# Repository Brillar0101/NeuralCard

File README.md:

# NeuralCard

A business card that runs a neural network.

> This is the sponsorship build, a fork of
> [NeuralCard](https://github.com/Brillar0101/NeuralCard) prepared for assembly by
> PCBWay. The BOM has been rewritten from JLCPCB and LCSC part codes into
> manufacturer part numbers PCBWay can quote, with approved alternates where a swap
> is safe and do-not-substitute rules where it is not. Revision v3.0.1-dev corrects
> the BOOT and RESET switch pad mapping after the prototype showed IO0/EN shorted to
> ground. This is still a development board: its latest DRC reports 410 violations
> and 191 schematic-parity issues. See the [verification report](docs/drc/v3.0.1-dev-verification.md)
> before using or fabricating this revision.

It is a credit-card-sized PCB, 85.6 by 54 mm, carrying an ESP32-S3, a 6-axis
IMU, and 24 LEDs laid out as the network it actually runs: 6 input neurons,
8 hidden, 10 output. You hold the card, draw a digit in the air, and the LEDs
light with the real activations as inference runs. Brightest output neuron
wins.

The front artwork is the network diagram. The synapse lines are drawn at three
stroke weights, the way a trained model's weights differ. There is also an NFC
tag with a coil antenna etched into the copper, so tapping a phone opens
[princetekki.com/card](https://www.princetekki.com/card) and offers a vCard.
That works with a dead battery, or no battery at all, because the phone's own
field powers the tag.

## Repository layout

| Path | What's in it |
|---|---|
| `hardware/` | KiCad 10 project: schematic, board, custom symbol and footprint libraries, 3D models |
| `fab/` | Manufacturing outputs: Gerber zip, drill files, pick-and-place, and three BOM/order files for PCBWay, JLCPCB, and LCSC |
| `firmware/` | ESP-IDF project. Charlieplex driver, IMU driver, gesture recorder. Builds today. |
| `docs/` | Design rationale, component sourcing, datasheet findings, DRC history, audits, FAQ |
| `hardware/datasheets/` | Component datasheets indexed to the v3.0.1-dev BOM |
| `render/` | The board renders used above |
| `CHANGELOG.md` | Revision history, newest first |

Start with [`docs/DESIGN.md`](docs/DESIGN.md) for why the board is shaped the
way it is, [`docs/FAQ.md`](docs/FAQ.md) for the questions people actually ask,
and [`docs/drc/README.md`](docs/drc/README.md) for the verification trail.

## Hardware

An ESP32-S3-WROOM-1-N8R2 does the thinking and runs the inference. An
LSM6DS3TR-C accelerometer and gyro sits on I2C, and its six axes map one to one
onto the six input neurons. The 24 red LEDs are charlieplexed across 6 GPIO
with software PWM for the glow.

For the business-card half there is an ST25DV04K dynamic NFC tag with a 9-turn
coil in the copper, tuned by a single external cap (C12) against the chip's
internal capacitance.

USB-C arrived in v2.3. The S3 has native USB, so a plain cable flashes the
board and gives a serial console without an adapter. A USBLC6-2SC6 protects the
data pair.

Power comes from a rechargeable LIR2450 coin cell or USB-C. U6 charges the cell
from USB at 50 mA; D25 and Q1 feed the VSYS node, and U3 regulates VSYS to 3.3 V.
Use a rechargeable LIR2450 only. Do not install a primary CR2450 on the charger.

Two copper layers with filled GND pours, set 0.5 mm inside the rounded board
edge. The latest development-board checks still report electrical and
schematic-parity issues; see the verification record before treating any net or
layout as fabrication-ready.

## How it's wired

Power and charging paths.

```mermaid
flowchart LR
    USB["USB-C · J2<br/>5 V VBUS"] --> D25["D25 · B5819W<br/>Schottky"]
    D25 --> VSYS[["VSYS"]]
    USB --> U6["U6 · MCP73831<br/>50 mA charger"]
    U6 -->|"charge"| BT1["BT1<br/>LIR2450 · rechargeable"]
    BT1 --> SW3{{"SW3 · MSK12C02<br/>battery switch"}}
    SW3 --> Q1{{"Q1 · AO3401A<br/>P-FET isolation"}}
    Q1 --> VSYS
    VSYS --> LDO["U3 · ME6211<br/>3.3 V LDO"]
    LDO --> RAIL[["+3V3 rail"]]
    RAIL --> U1["ESP32-S3"]
    RAIL --> U2["LSM6DS3TR-C"]
    RAIL --> U4["ST25DV04K"]
    RAIL --> LEDS["24 LEDs<br/>charlieplexed"]

    classDef src fill:#F0AB00,stroke:#795600,color:#151515
    classDef sw fill:#0066CC,stroke:#003366,color:#FFFFFF
    classDef rail fill:#009596,stroke:#005F60,color:#FFFFFF
    classDef load fill:#F0F0F0,stroke:#8A8D90,color:#151515
    classDef off fill:#FFFFFF,stroke:#C9190B,color:#C9190B,stroke-dasharray:4 3
    class USB,BT1 src
    class SW3,Q1,LDO sw
    class RAIL rail
    class U1,U2,U4,LEDS load
    class NC off
```

Then data. USB-C carries both power and programming. NFC is independent of
both and needs no power of its own.

```mermaid
flowchart LR
    HOST(["laptop"]) -->|"USB-C · D+/D-"| ESD["U5 · USBLC6<br/>ESD array"]
    ESD -->|"native USB-Serial-JTAG"| U1["ESP32-S3"]
    U1 <-->|I2C| U2["IMU"]
    U1 <-->|I2C| U4["NFC tag"]
    U2 -.->|"motion interrupt"| U1
    U4 -.->|"field-detect GPO"| U1
    PHONE(["phone"]) -.->|"13.56 MHz field<br/>powers the tag"| U4
    U1 --> LEDS["24 LEDs"]

    classDef ext fill:#F0AB00,stroke:#795600,color:#151515
    classDef chip fill:#0066CC,stroke:#003366,color:#FFFFFF
    classDef out fill:#3E8635,stroke:#1F4D19,color:#FFFFFF
    class HOST,PHONE ext
    class ESD,U1,U2,U4 chip
    class LEDS out
```

And inference. The six IMU axes feed the six input neurons, and the LEDs at
each node light with the real activations as the network runs.

```mermaid
flowchart LR
    IMU["LSM6DS3TR-C<br/>ax ay az · gx gy gz"] --> IN["INPUT<br/><b>6 neurons</b>"]
    IN --> HID["HIDDEN<br/><b>8 neurons</b>"]
    HID --> OUT["OUTPUT<br/><b>10 neurons</b><br/>digits 0-9"]
    OUT --> GUESS(["brightest neuron<br/>= the guess"])

    classDef sensor fill:#F0AB00,stroke:#795600,color:#151515
    classDef layer fill:#0066CC,stroke:#003366,color:#FFFFFF
    classDef out fill:#5752D1,stroke:#2A265F,color:#FFFFFF
    classDef result fill:#3E8635,stroke:#1F4D19,color:#FFFFFF
    class IMU sensor
    class IN,HID layer
    class OUT out
    class GUESS result
```

All 24 LEDs run from 6 GPIO by charlieplexing. That is why there are 6
current-limiting resistors rather than 24, and why the display works on a coin
cell at all: only one LED is ever actually lit.

## Firmware

`firmware/` is an ESP-IDF project that builds today. It has the charlieplex
driver, with the LED-to-pin mapping extracted from the board netlist rather
than guessed, the LSM6DS3 driver, and a motion-triggered gesture recorder that
prints labelled CSV over the USB-C console. That recorder is how you build a
training set.

```
cd firmware && idf.py set-target esp32s3 && idf.py build && idf.py flash monitor
```

The neural network itself is deliberately not in the repo yet: it has to be
trained on gestures recorded from real hands, which needs assembled boards.
See [`firmware/README.md`](firmware/README.md).

## Ordering

Everything a fab needs is in `fab/`: `NeuralCard_gerbers.zip` (gerbers +
drill), `NeuralCard-cpl.csv` (placements), and a BOM. Use
`BOM_PCBWay.csv` for this build, which carries manufacturer part numbers,
approved alternates, and per-line substitution rules. `BOM_JLCPCB.csv` is the
upstream file and is keyed to LCSC codes instead.

Build spec: 2 layers, 1.6 mm thickness, green soldermask, HASL. That is the
cheap prototype configuration, currently about $2 for five boards.

Two finish options are worth knowing about if you ever make a batch to hand
out. At 0.8 mm the board feels like a card instead of a circuit board. With
ENIG, the hairline under the name comes out gold, since it is a mask opening
over the ground pour and plates with whatever finish you pick. Both cost more.
Neither changes the gerbers, so they are order-time choices.

**Two build routes:**

Hand assembly means ordering bare boards plus a solder-paste stencil and
buying parts from LCSC. It is the cheapest route, and the stencil is what makes
the LGA-14 IMU tractable with hot air.

Factory assembly means turnkey PCBA on both sides. It adds roughly $100 of fixed
setup and feeder cost at a typical prototype house, so it only pays off around 30
boards or more. This build is being assembled by PCBWay under sponsorship, so see
[`docs/SOURCING.md`](docs/SOURCING.md) for how the parts are actually bought.

Two BOM notes. C12, the NFC tuning cap, ships as 68 pF and should be retuned
against the coil once it exists. Read range is the practical test. The NFC chip
is ST25DV04KC-IE6S3, which is the active part. The older ST25DV04K-IER6S3 is
marked not recommended for new designs but is still widely stocked, and it is
listed as the approved fallback: same package, same pinout, same function.

## Status

The released v2.3.1 tag is unchanged. The working v3.0.1-dev revision corrects
the tactile-switch pad assignment that grounded BOOT and RESET on the prototype.
Its DRC reports 410 violations, 191 schematic-parity issues, and 0 unconnected
items; ERC reports 42 library-configuration warnings. It is not ready for
fabrication. See [`docs/drc/v3.0.1-dev-verification.md`](docs/drc/v3.0.1-dev-verification.md)
for the full reports and [`hardware/datasheets/README.md`](hardware/datasheets/README.md)
for the component document index.

The firmware scaffold builds. Drivers and gesture capture work. The trained
model is the remaining piece, and it needs assembled boards before it can
exist.

So today the card is a very elaborate NFC business card, and that part works
the moment the tag is programmed.

## License

CERN-OHL-P v2. See [LICENSE](LICENSE). Do whatever you want with it,
attribution appreciated.

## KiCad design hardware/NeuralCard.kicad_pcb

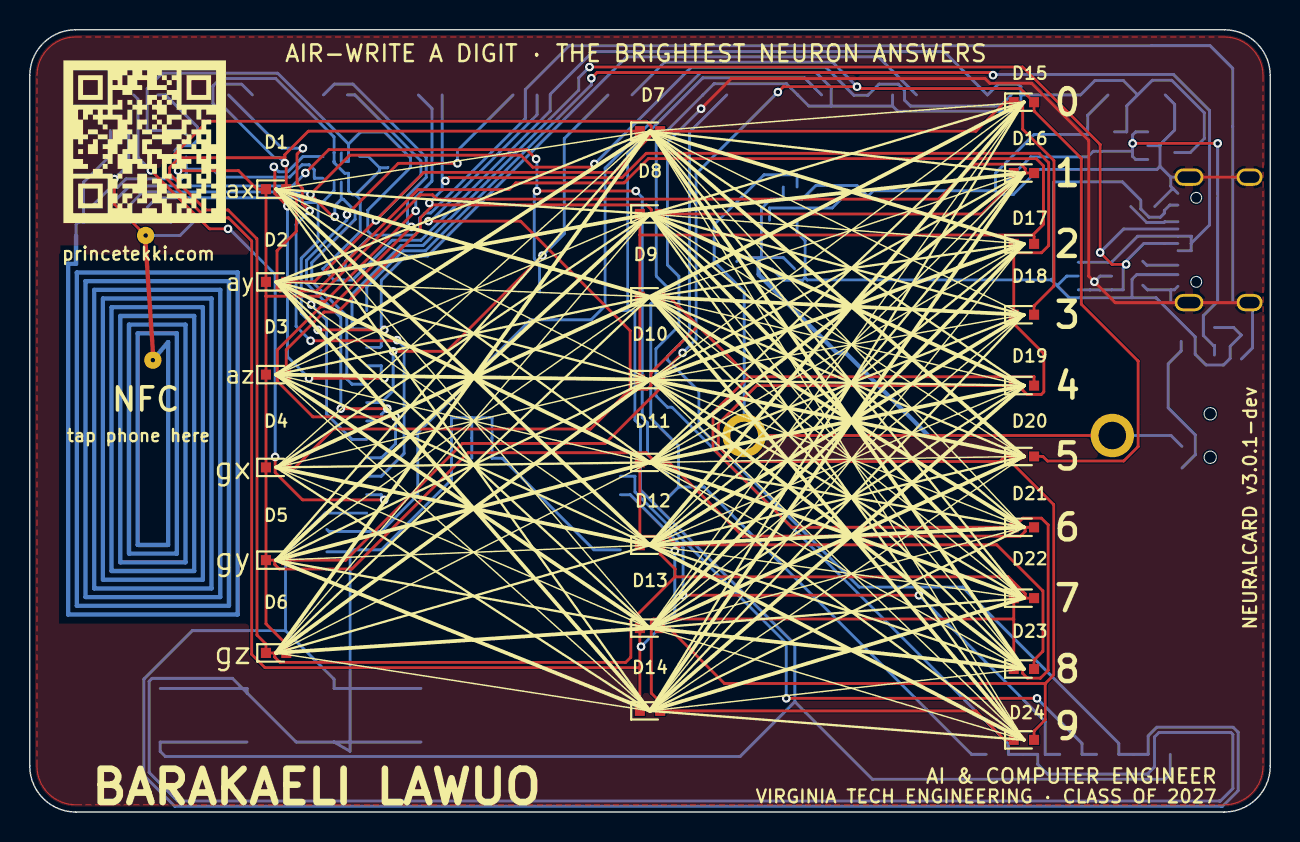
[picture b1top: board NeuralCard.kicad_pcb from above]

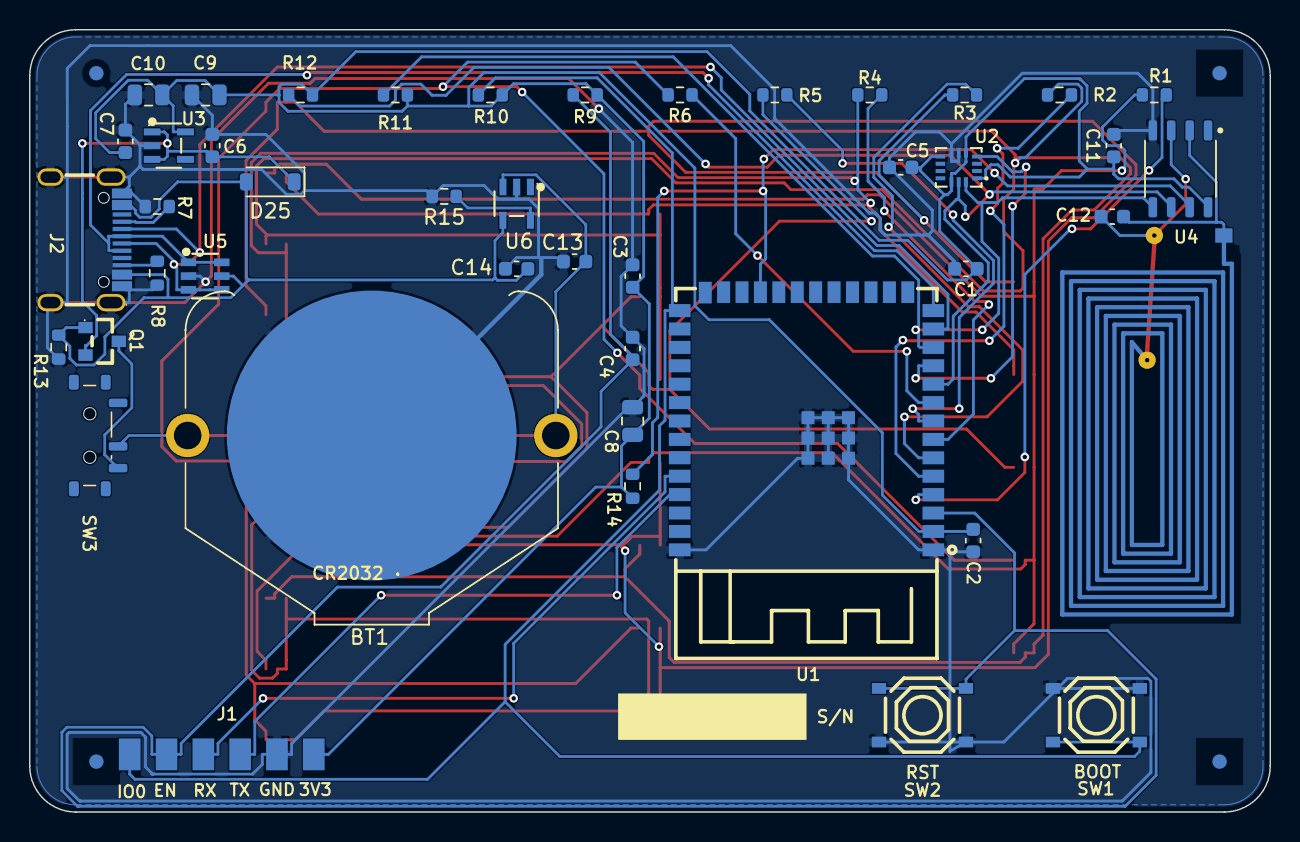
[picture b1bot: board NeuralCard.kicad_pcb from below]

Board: 2 copper layers, 85.6 x 54.0 mm, 72 parts (48 on the bottom side), 33 nets.

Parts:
ANT1: NFC_COIL; NFC_Antenna_13x24
BT1: LIR2450; BatteryHolder_Keystone_3009_1x2450
C1, C2, C3, C4, C5, C11, C12: C_0603_1608Metric
C6, C7: 1uF; C_0603_1608Metric
C8, C9, C10: C_0805_2012Metric
C13, C14: 4.7uF; C_0603_1608Metric
D1, D2, D3, D4, D5, D6, D7, D8, D9, D10, D11, D12, D13, D14, D15, D16, D17, D18, D19, D20, D21, D22, D23, D24: LED-SMD_L1.6-W0.8-R-RD
D25: B5819W; D_SOD-123
FID1, FID2, FID3, FID4: Fiducial_1mm_Mask2mm
J1: ProgPads; ProgPads_1x6
J2: TYPE-C-31-M-12; USB-C_SMD-TYPE-C-31-M-12_1
Q1: AO3401A; SOT-23_L2.9-W1.3-P1.90-LS2.4-BR
R1, R2, R3, R4, R5, R6, R9, R10, R11, R12, R14: R_0603_1608Metric
R7, R8: 5.1k; R_0603_1608Metric
R13: 100k; R_0603_1608Metric
R15: 20k; R_0603_1608Metric
SW1, SW2: SW-SMD_4P-L5.1-W5.1-P3.70-LS6.5-TL_H1.5
SW3: SW_SPDT_Shouhan_MSK12C02
U1: WIRELM-SMD_ESP32-S3-WROOM-1
U2: LGA-14_L3.0-W2.5-P0.50-TL
U3: ME6211C33M5G-N; SOT-23-5_L3.0-W1.7-P0.95-LS2.8-BL
U4: SO-8_L4.9-W3.9-P1.27-LS5.9-BL
U5: USBLC6-2SC6; SOT-23-6_L2.9-W1.6-P0.95-LS2.8-BL
U6: MCP73831T-2ACI/OT; SOT-23-5_L3.0-W1.7-P0.95-LS2.8-BL

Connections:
+3V3: C1.1, C2.1, C3.1, C5.1, C7.1, C8.1, C9.1, C10.1, C11.1, J1.1, R9.1, R10.1, R11.1, R12.1, R14.1, U1.2, U2.1, U2.5, U2.8, U2.12, U3.5, U4.8
CC1: J2.A5, R7.1
CC2: J2.B5, R8.1
CHX1: R1.1, U1.4
CHX2: R2.1, U1.5
CHX3: R3.1, U1.6
CHX4: R4.1, U1.7
CHX5: R5.1, U1.8
CHX6: R6.1, U1.9
CP1: D1.2, D2.2, D3.2, D4.2, D5.2, D6.1, D11.1, D16.1, D21.1, R1.2
CP2: D1.1, D6.2, D7.2, D8.2, D9.2, D10.2, D12.1, D17.1, D22.1, R2.2
CP3: D2.1, D7.1, D11.2, D12.2, D13.2, D14.2, D15.2, D18.1, D23.1, R3.2
CP4: D3.1, D8.1, D13.1, D16.2, D17.2, D18.2, D19.2, D20.2, D24.1, R4.2
CP5: D4.1, D9.1, D14.1, D19.1, D21.2, D22.2, D23.2, D24.2, R5.2
CP6: D5.1, D10.1, D15.1, D20.1, R6.2
EN: C4.1, J1.5, R9.2, SW2.3, SW2.4, U1.3
GND: BT1.2, C1.2, C2.2, C3.2, C4.2, C5.2, C6.2, C7.2, C8.2, C9.2, C10.2, C11.2, C13.2, C14.2, J1.2, J2.1, J2.2, J2.3, J2.4, J2.A1B12, J2.B1A12, R7.2, R8.2, R13.2, R15.2, SW1.3, SW1.4, SW2.1, SW2.2, U1.1, U1.40, U1.41, U2.6, U2.7, U3.2, U4.4, U5.2, U6.2
IMU_INT: U1.11, U2.4
IO0: J1.6, R10.2, SW1.1, SW1.2, U1.27
NFC_ANT_A: ANT1.1, C12.1, U4.2
NFC_ANT_B: ANT1.2, C12.2, U4.3
NFC_GPO: R14.2, U1.23, U4.7
PROG: R15.1, U6.5
RXD: J1.4, U1.36
SCL: R12.2, U1.10, U2.13, U4.6
SDA: R11.2, U1.12, U2.14, U4.5
TXD: J1.3, U1.37
USB_DM: J2.A7, J2.B7, U1.13, U5.3, U5.4
USB_DP: J2.A6, J2.B6, U1.14, U5.1, U5.6
VBAT: BT1.1, C13.1, SW3.2, U6.3
VBAT_SW: Q1.3, SW3.3
VBUS: C14.1, D25.2, J2.A4B9, J2.B4A9, Q1.1, R13.1, U5.5, U6.4
VSYS: C6.1, D25.1, Q1.2, U3.1, U3.3

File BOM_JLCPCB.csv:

Comment,Designator,Footprint,LCSC Part #
"ESP32-S3-WROOM-1-N8R2 (C2913204 is the N8R2 variant; pick an N16R8 ID at order if the bigger memory is wanted)",U1,WIRELM-SMD_ESP32-S3-WROOM-1,C2913204
"LSM6DS3TR-C",U2,LGA-14_L3.0-W2.5-P0.50-TL,C967633
"CR2032-BS-6-1 holder",BT1,BAT-TH_CR2032-BS-6-1,C70377
"TS-1187A tact (BOOT)",SW1,SW-SMD_4P-L5.1-W5.1-P3.70-LS6.5-TL_H1.5,C318884
"TS-1187A tact (RESET)",SW2,SW-SMD_4P-L5.1-W5.1-P3.70-LS6.5-TL_H1.5,C318884
"Red LED 0603",D1,LED-SMD_L1.6-W0.8-R-RD,C2286
"Red LED 0603",D2,LED-SMD_L1.6-W0.8-R-RD,C2286
"Red LED 0603",D3,LED-SMD_L1.6-W0.8-R-RD,C2286
"Red LED 0603",D4,LED-SMD_L1.6-W0.8-R-RD,C2286
"Red LED 0603",D5,LED-SMD_L1.6-W0.8-R-RD,C2286
"Red LED 0603",D6,LED-SMD_L1.6-W0.8-R-RD,C2286
"Red LED 0603",D7,LED-SMD_L1.6-W0.8-R-RD,C2286
"Red LED 0603",D8,LED-SMD_L1.6-W0.8-R-RD,C2286
"Red LED 0603",D9,LED-SMD_L1.6-W0.8-R-RD,C2286
"Red LED 0603",D10,LED-SMD_L1.6-W0.8-R-RD,C2286
"Red LED 0603",D11,LED-SMD_L1.6-W0.8-R-RD,C2286
"Red LED 0603",D12,LED-SMD_L1.6-W0.8-R-RD,C2286
"Red LED 0603",D13,LED-SMD_L1.6-W0.8-R-RD,C2286
"Red LED 0603",D14,LED-SMD_L1.6-W0.8-R-RD,C2286
"Red LED 0603",D15,LED-SMD_L1.6-W0.8-R-RD,C2286
"Red LED 0603",D16,LED-SMD_L1.6-W0.8-R-RD,C2286
"Red LED 0603",D17,LED-SMD_L1.6-W0.8-R-RD,C2286
"Red LED 0603",D18,LED-SMD_L1.6-W0.8-R-RD,C2286
"Red LED 0603",D19,LED-SMD_L1.6-W0.8-R-RD,C2286
"Red LED 0603",D20,LED-SMD_L1.6-W0.8-R-RD,C2286
"Red LED 0603",D21,LED-SMD_L1.6-W0.8-R-RD,C2286
"Red LED 0603",D22,LED-SMD_L1.6-W0.8-R-RD,C2286
"Red LED 0603",D23,LED-SMD_L1.6-W0.8-R-RD,C2286
"Red LED 0603",D24,LED-SMD_L1.6-W0.8-R-RD,C2286
"220R 0603",R1,R0603,C22962
"220R 0603",R2,R0603,C22962
"220R 0603",R3,R0603,C22962
"220R 0603",R4,R0603,C22962
"220R 0603",R5,R0603,C22962
"220R 0603",R6,R0603,C22962
"10k 0603",R9,R0603,C25804
"10k 0603",R10,R0603,C25804
"4.7k 0603",R11,R0603,C23162
"4.7k 0603",R12,R0603,C23162
"100nF 0603",C1,C0603,C14663
"100nF 0603",C2,C0603,C14663
"100nF 0603",C3,C0603,C14663
"100nF 0603",C4,C0603,C14663
"100nF 0603",C5,C0603,C14663
"10uF 0805",C8,C0805,C15850
"22uF 0805",C9,C0805,C45783
"22uF 0805 (subst: no basic 100uF in 0805; consider 1206/100uF next rev)",C10,C0805,C45783
"ST25DV04KC-IE6S3 NFC tag",U4,SO-8_L4.9-W3.9-P1.27-LS5.9-BL,C3304276
"100nF 0603",C11,C0603,C14663
"62pF NP0 0603 (tune after VNA; 56-68pF window)",C12,C0603,select-at-order
"100k 0603",R14,R0603,C25803
"SPDT slide switch (tiny SMD, 3-pad ~1.3mm pitch) - POWER on/off, in series with coin cell + terminal; verify footprint vs chosen part",SW3,gc_SlideSPDT_3P,select-at-order

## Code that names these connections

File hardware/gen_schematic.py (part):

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    s2 = ep(sx, sy, "Switch:SW_SPDT", "2")       # common pole
    s3 = ep(sx, sy, "Switch:SW_SPDT", "3")       # closed throw
    tap_label("VBAT", s2[0], s2[1], dx=-2.54, just="right")
    # throw -> VBAT_SW, dropped downward so the label clears C8's +3V3 symbol
    lx_, ly_ = round(s3[0] + 2.54, 4), round(s3[1] + 5.08, 4)
    wire(s3[0], s3[1], lx_, s3[1])
    wire(lx_, s3[1], lx_, ly_)
    glabel("VBAT_SW", lx_, ly_, 90, "right")
    no_connect(s1[0], s1[1])

    # --- Bulk / ride-out caps on +3V3: C8 10uF, C9 22uF, C10 100uF ---
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    # No PWR_FLAGs: every power net now has a real power_out driver, so a flag
    # would collide (pin_to_pin power_out vs power_out -- the old ERC errors).
    # GND and VBAT are driven by BT1 (pins typed power_out), +3V3 by U3 VOUT,
    # VBUS by J2's VBUS pins. VBAT_SW carries only passive pins (SW3, Q1
    # source), which ERC does not require a driver for.


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        specs[str(n)] = ("nc",)
    for n in range(28, 40):       # right-side unused (incl. 35/36/37 PSRAM)
        specs[str(n)] = ("nc",)
    specs["36"] = ("lbl", "RXD")  # RXD0 (GPIO44) -> prog header RX
    specs["37"] = ("lbl", "TXD")  # TXD0 (GPIO43) -> prog header TX
    specs["23"] = ("lbl", "NFC_GPO")  # GPIO21 <- ST25DV field-detect interrupt
    for n in range(1, 42):
        pn = str(n)
        px, py = ep(ux, uy, esp, pn)
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        "4": ("gnd",),
        "5": ("lbl", "SDA"),             # shared bus with IMU (addrs differ)
        "6": ("lbl", "SCL"),
        "7": ("lbl", "NFC_GPO"),         # open-drain field-detect -> GPIO21
        "8": ("pwr", "+3V3"),
    }
    for n in range(1, 9):
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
